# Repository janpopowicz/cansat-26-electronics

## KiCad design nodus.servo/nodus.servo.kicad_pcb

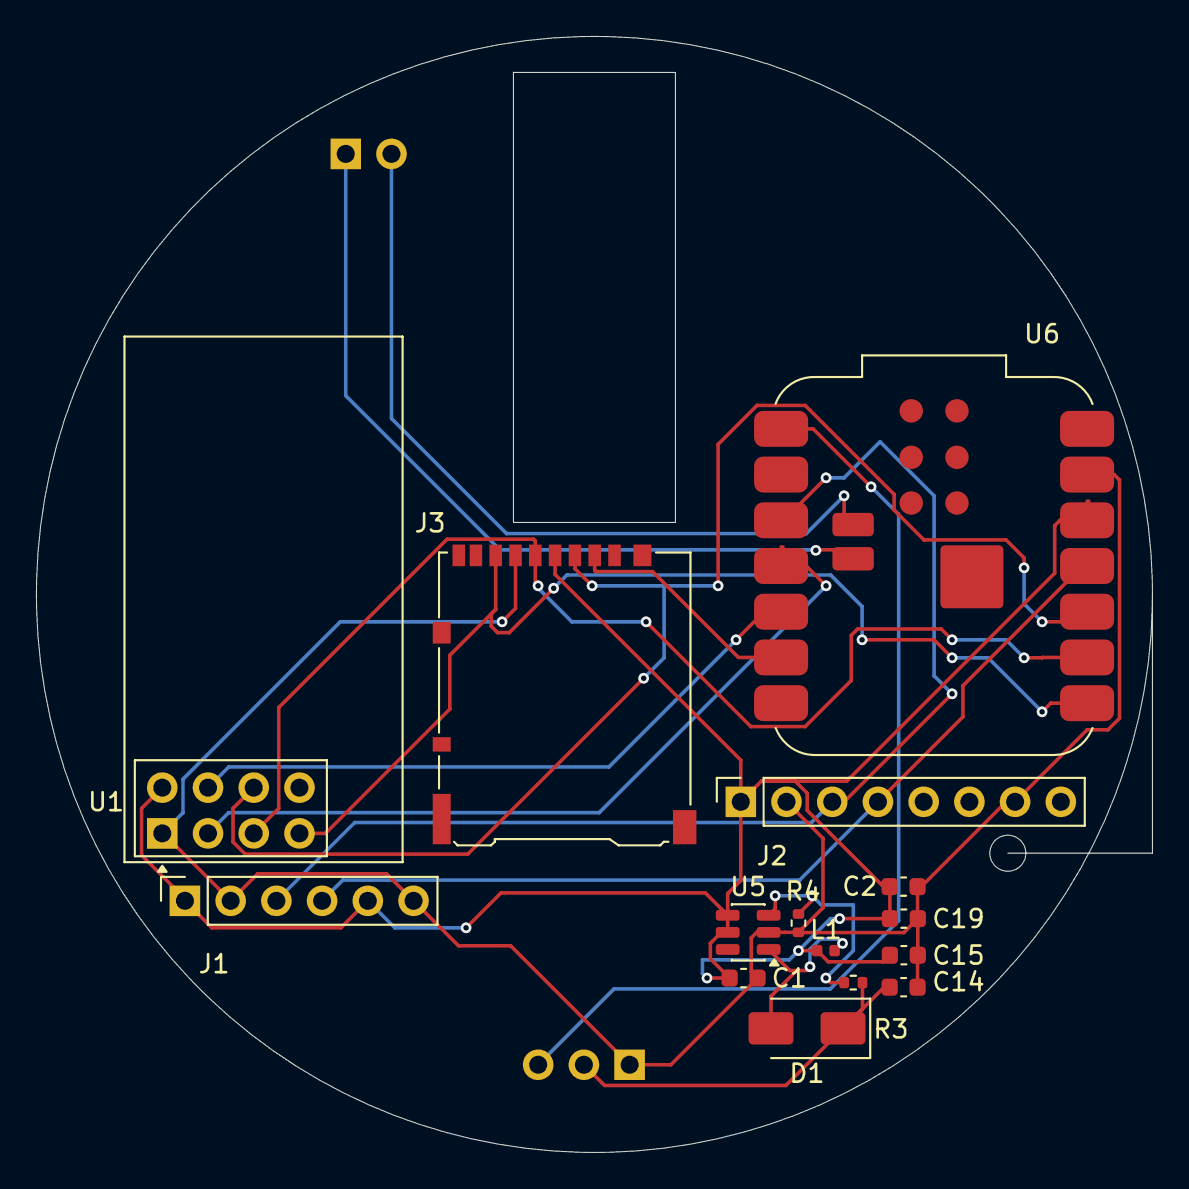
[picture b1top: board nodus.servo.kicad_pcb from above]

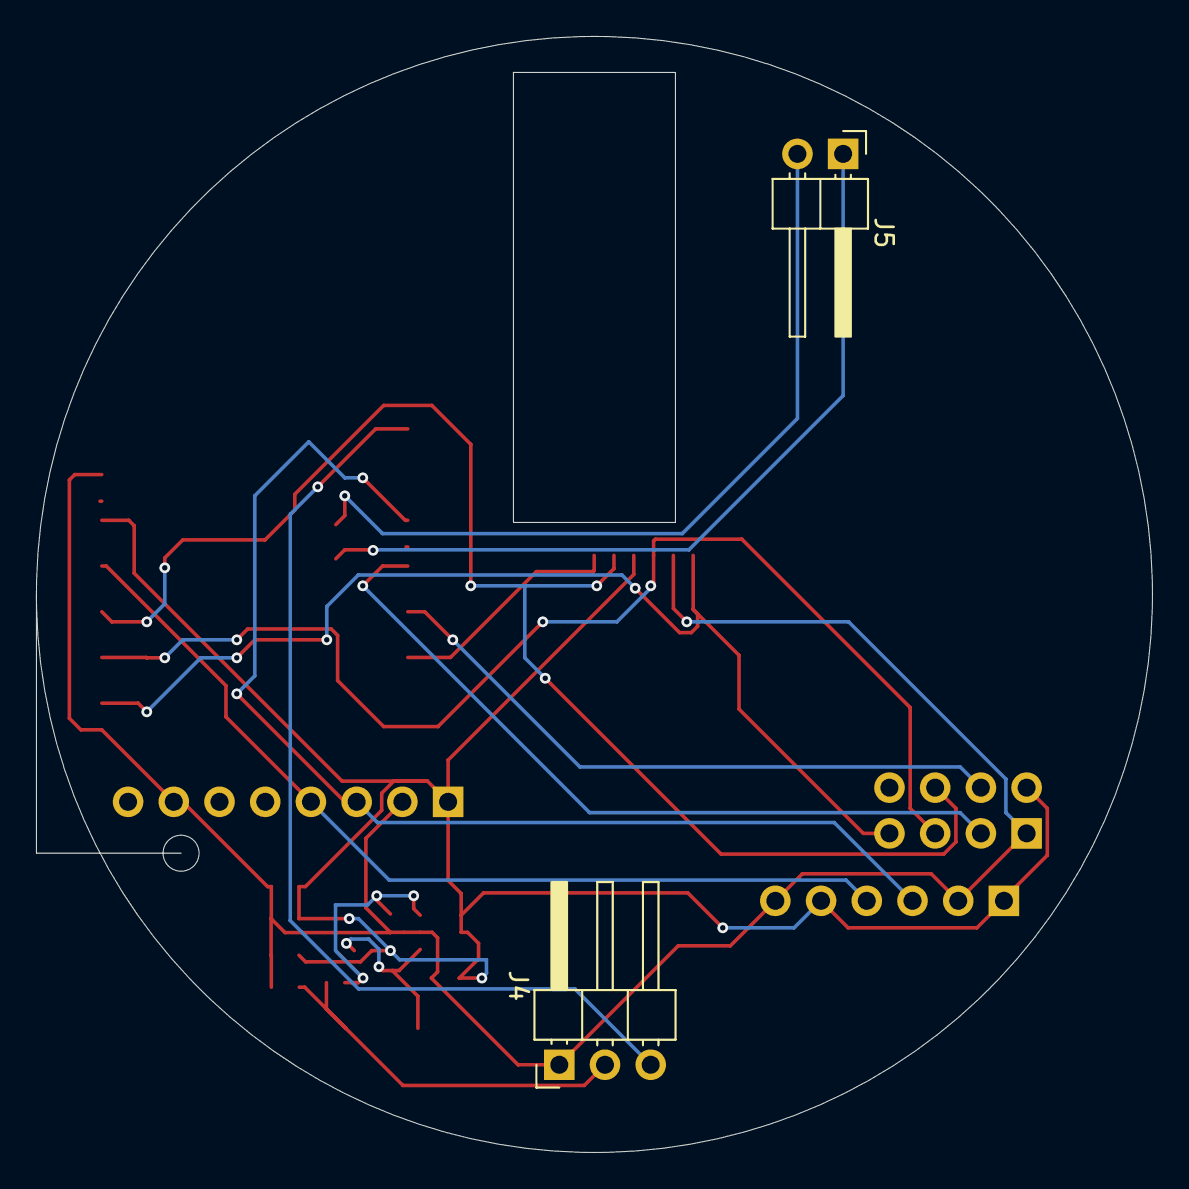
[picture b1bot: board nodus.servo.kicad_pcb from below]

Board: 2 copper layers, 62.0 x 62.0 mm, 17 parts (2 on the bottom side), 16 nets.

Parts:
C1: 10u; C_0603_1608Metric
C2: 100n; C_0603_1608Metric
C14, C15: 22u; C_0603_1608Metric
C19: 0.1u; C_0603_1608Metric
D1: SS34; D_SMA
J1: Conn1x6_BME; PinSocket_1x06_P2.54mm_Vertical
J2: Conn1x8_MPU; PinSocket_1x08_P2.54mm_Vertical
J3: Micro_SD_Card; microSD_HC_Hirose_DM3AT-SF-PEJM5
J4: Conn_01x03_Pin; PinHeader_1x03_P2.54mm_Horizontal
J5: Conn_01x02_Pin; PinHeader_1x02_P2.54mm_Horizontal
L1: 22uH; L_0402_1005Metric
R3: 12k; R_0402_1005Metric
R4: 88k; R_0402_1005Metric
U1: NRF24L01; nRF24L01_Breakout
U5: MT3608; SOT-23-6
U6: XIAO ESP32C3; MCU_Seeed_ESP32C3

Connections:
+3.3V: C1.1, C2.1, C15.1, C19.2, J1.1, J1.5, J2.1, J3.4 (VDD), L1.1, U1.2 (VCC), U5.4 (EN), U5.5 (IN), U6.12 (VCC_3V3)
BATGND: J5.2, U6.17
BATIN: J5.1, U6.16
GND: C1.2, C2.2, C14.2, C15.2, C19.1, J1.2, J1.6, J2.2, J2.7, J3.6 (VSS), J4.1, R4.2, U1.1 (GND), U5.2 (GND), U6.13 (GND)
I2C_SCL: J1.3, J2.3, U6.3 (D2)
I2C_SDA: J1.4, J2.4, U6.11 (D10)
NRF_CE: U1.3 (CE), U6.4 (D3)
NRF_CSN: U1.4 (~CSN), U6.5 (D4)
unnamed: D1.2 (A), L1.2, U5.1 (SW)
unnamed: C14.1, D1.1 (K), J4.2, R3.1
unnamed: R3.2, R4.1, U5.3 (FB)
SD_CS: J3.2 (DAT3/CD), U6.6 (D5)
SERVO_PWM: J4.3, U6.1 (D0)
SPI_MISO: J3.7 (DAT0), U1.7 (MISO), U6.8 (D7)
SPI_MOSI: J3.3 (CMD), U1.6 (MOSI), U6.10 (D9)
SPI_SCK: J3.5 (CLK), U1.5 (SCK), U6.9 (D8)
